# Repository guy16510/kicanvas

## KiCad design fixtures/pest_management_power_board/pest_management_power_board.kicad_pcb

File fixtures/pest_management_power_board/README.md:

# Pest Management Power Distribution Board

Rev B KiCad fixture for a low-voltage battery/control board that interfaces to a sealed commercial high-voltage DC/DC module used with a three-layer insect mesh.

## Rev B design goal

The battery source is treated as a protected 2S pack with **unknown cell current capability**. The PCB is therefore designed to minimize low-voltage losses and support short module-input transients, while a replaceable input fuse deliberately limits battery current.

This revision does **not** assume miscellaneous 18650 cells are safely capable of 5 A. Do not assemble unmatched loose cells into a 2S pack. Use a BMS/protected pack and begin with the conservative fuse value in the BOM.

## Electrical architecture

- Protected 2S Li-ion input, 7.4 V nominal / 8.4 V fully charged
- F1: 5x20 mm fast fuse, **start at 2 A** because cell capability is unknown
- SW1: panel-mounted momentary switch with an oversized low-resistance DC current path
- C1 + C2: two 2200 uF / 16 V low-ESR capacitors in parallel at the HV-module input
- C3: 1 uF / 25 V fast bypass capacitor across the switched module input
- Total bulk capacitance: nominal 4400 uF
- 3.0 mm low-voltage power traces to reduce distribution loss
- J2, 4-position isolated landing interface to a sealed commercial HV module
  - Pin 1: +7.4V_SW
  - Pin 2: GND
  - Pin 3: HV_POS
  - Pin 4: HV_NEG
- J3: HV_POS external mesh terminal
- J4: HV_NEG external mesh terminal

## What the larger capacitor bank does

The C1/C2 bank does not create additional sustained power. It stores a small amount of energy locally and can reduce battery-voltage sag during a short input-current transient from the commercial HV module. Sustained output power is still limited by the cells, BMS, fuse and module efficiency.

At 8.4 V, 4400 uF stores roughly 0.16 joule. At 7.4 V it stores roughly 0.12 joule. This is useful as a local transient reservoir, not as a substitute for a higher-power battery pack.

## PCB constraints

- `LV_Power`: battery, fuse, switch, capacitor bank, module input and return
- `HV_Grid`: commercial module HV output to J3/J4
- `HV_Grid` minimum clearance: 10.0 mm
- HV_POS and HV_NEG run in separate straight corridors
- A 2 mm-wide routed Edge.Cuts slot runs between the two HV corridors
- LV routing is kept left of the HV_POS corridor with >10 mm intended copper-edge spacing

## Power strategy with the same batteries

1. Reduce resistance in the low-voltage path using larger pads, 3 mm traces and an oversized switch contact path.
2. Put low-ESR bulk capacitance physically close to the module input.
3. Let the fuse control maximum battery current. Start at 2 A with unknown cells.
4. The sealed commercial HV module remains the component that determines sustained mesh voltage/current and recovery rate.

## Safety note

The board does not generate high voltage. It only distributes low-voltage battery power and interfaces to a sealed, commercially manufactured high-voltage module. Actual HV connector ratings, spacing, enclosure design, touch protection, discharge behavior and compliance must be validated against the selected module's maximum output voltage and applicable product-safety standards before fabrication or use.

The PCB being physically capable of carrying several amps does not mean unknown 18650 cells can safely supply that current.

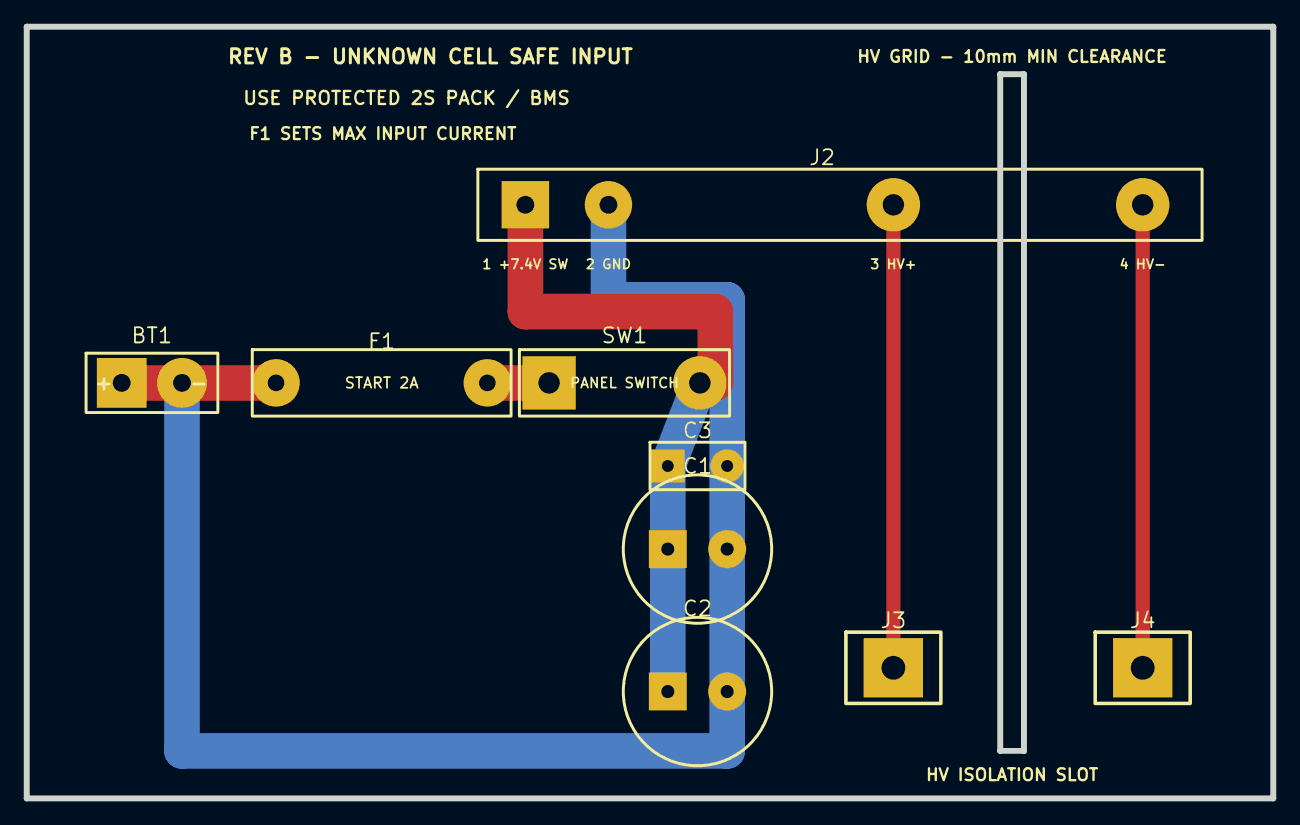
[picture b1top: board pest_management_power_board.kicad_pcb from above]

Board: 2 copper layers, 105.0 x 65.0 mm, 9 parts (0 on the bottom side), 6 nets.

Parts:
BT1: PROTECTED_2S_18650_7.4V; BATTERY_2S_INPUT_5P08
C1, C2: 2200uF_16V_LOW_ESR; CP_RADIAL_12P5MM_P5
C3: 1uF_25V_FILM; FILM_CAP_P5
F1: START_2A_FAST_MAX_AFTER_CELL_VALIDATION; FUSE_5X20_CLIP_17.8MM
J2: SEALED_COMMERCIAL_HV_MODULE_INTERFACE; HV_MODULE_4PIN_ISOLATED
J3: HV_POS_GRID; HV_GRID_SINGLE_SCREW_TERMINAL
J4: HV_NEG_GRID; HV_GRID_SINGLE_SCREW_TERMINAL
SW1: MOMENTARY_NO_10A_DC_PATH; PANEL_SWITCH_10A_LEADS

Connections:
+7V4_BAT: BT1.1, F1.1
+7V4_FUSED: F1.2, SW1.1
+7V4_SW: C1.1, C2.1, C3.1, J2.1, SW1.2
GND: BT1.2, C1.2, C2.2, C3.2, J2.2
HV_NEG: J2.4, J4.1
HV_POS: J2.3, J3.1

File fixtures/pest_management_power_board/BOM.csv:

Reference,Qty,Function,Specification,Recommended Part / Family,Notes
BT1,1,Battery input,2S Li-ion 7.4V nominal input; connector rated >=5A,"Phoenix Contact MKDS 1,5/2 family or equivalent 2-position 5.08mm terminal",Use protected 2S pack/BMS; connector and wiring must be rated for pack fault current
F1,1,Overcurrent fuse,5A fast-acting 5x20mm cartridge,"Littelfuse 217 Series, 5A fast-acting, e.g. 0217005.MXP",Confirm interrupt rating is appropriate for the selected battery pack
F1-HOLDER,1,Fuse holder,5x20mm PCB clip/holder rated >=5A,"Bel / Stewart FC-203-22 style 5x20mm holder or equivalent",PCB footprint uses 17.8mm lead spacing
SW1,1,Momentary pushbutton,Normally-open momentary; >=5A DC continuous at the actual battery voltage,"Panel-mount industrial momentary switch, 5A DC minimum",Board uses two heavy through-hole lead pads rather than a low-current tactile switch footprint; select final MPN by verified DC rating
C1,1,Bulk decoupling capacitor,470uF 25V radial electrolytic; 105C preferred,"Panasonic FR/FC series or Nichicon PW/HE equivalent, 470uF 25V",PCB footprint assumes approximately 10mm diameter and 5mm lead pitch; confirm dimensions before fabrication
J2,1,Commercial HV module interface,4 electrical positions: Pin1 +7.4V_SW; Pin2 GND; Pin3 HV_POS; Pin4 HV_NEG,"Custom isolated 4-position interface / flying-lead landing pads",HV pins are intentionally separated from LV pins and from one another; do not substitute a standard 5mm-pitch 4-position block
J3,1,HV positive grid output,Single heavy screw terminal; voltage rating >= selected module maximum output,"HV-rated single-position barrier/screw terminal",Final MPN cannot be selected safely until module maximum output voltage and required creepage category are known
J4,1,HV negative grid output,Single heavy screw terminal; voltage rating >= selected module maximum output,"HV-rated single-position barrier/screw terminal",Final MPN cannot be selected safely until module maximum output voltage and required creepage category are known
HV-MODULE,1,Isolated high-voltage source,Sealed pre-fabricated commercial DC/DC step-up module; 7.4V-compatible input,"User-selected commercial encapsulated module",Not designed or fabricated on this PCB; verify output voltage/current, insulation rating, discharge behavior, enclosure and connector requirements
PCB,1,Printed circuit board,2-layer FR4 1.6mm; routed isolation slot; 10mm HV clearance rule,"Custom PCB",Use routed mechanical slot exactly as Edge.Cuts; fabrication drawing should explicitly call out slot

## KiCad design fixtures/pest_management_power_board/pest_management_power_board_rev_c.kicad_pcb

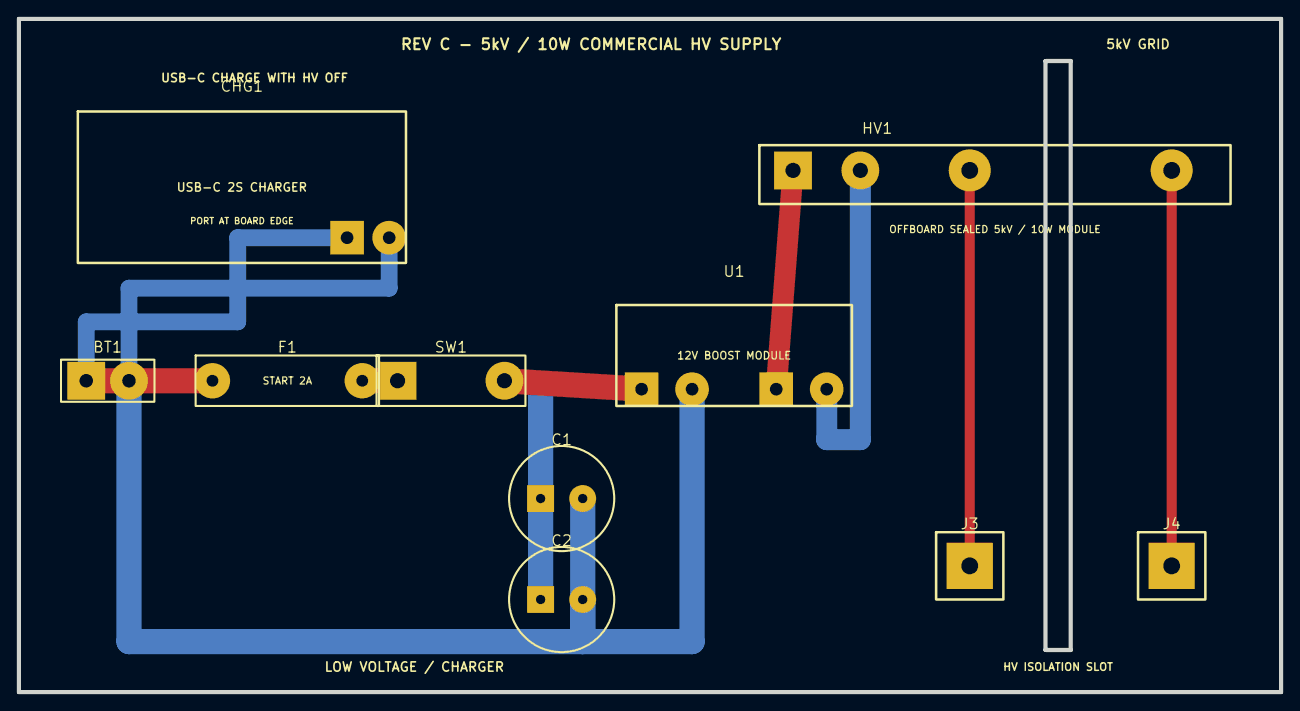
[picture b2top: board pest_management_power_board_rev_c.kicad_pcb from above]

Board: 2 copper layers, 150.0 x 80.0 mm, 10 parts (0 on the bottom side), 7 nets.

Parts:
BT1: PROTECTED_BALANCED_2S_PACK; PROTECTED_2S_PACK_INPUT
C1, C2: 2200uF_16V_LOW_ESR; CP_RADIAL_12P5_P5
CHG1: USB-C_5V_TO_2S_8V4_1A; USB_C_2S_CHARGER_DAUGHTERBOARD_39X18
F1: 2A_FAST_START; FUSE_5X20_CLIP_17P8
HV1: ANALOG_TECH_AHV12V5KV2MAW_OFFBOARD; AHV12V5KV2MAW_INTERFACE
J3: HV_POS_GRID; HV_GRID_SINGLE_TERMINAL
J4: HV_NEG_GRID; HV_GRID_SINGLE_TERMINAL
SW1: HV_ENABLE_MOMENTARY; PANEL_SWITCH_HEAVY
U1: POLOLU_U3V70F12_12V_BOOST; POLULU_U3V70F12_INTERFACE

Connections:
+12V_HV: HV1.1, U1.3
BAT_FUSED: F1.2, SW1.1
BAT_P: BT1.1, CHG1.1, F1.1
BAT_SW: C1.1, C2.1, SW1.2, U1.1
GND: BT1.2, C1.2, C2.2, CHG1.2, HV1.2, U1.2, U1.4
HV_NEG: HV1.4, J4.1
HV_POS: HV1.3, J3.1

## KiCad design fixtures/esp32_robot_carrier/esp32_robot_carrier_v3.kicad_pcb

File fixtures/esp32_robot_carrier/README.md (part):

# ESP32 robot carrier: 36–42 V input, 5 V/24 V power, and battery sensing

The generated v3 carrier accepts a 36–42 V battery, protects the input with the
LTC4367 stage, and feeds two isolated through-hole DC-DC modules: a regulated
5.10 V nominal rail for the Raspberry Pi, ESP32 peripherals, sensors, and RGB pixels, plus
a separately fused 24 V / 2.5 A rail for a servo. The protected battery voltage
is exposed to the ESP32 on GPIO34. A dual rail-to-rail amplifier lets the two
ESP32 DACs cover the exact WinXu controllers' approximately 1.1–4.2 V throttle
range. Four PhotoMOS relays provide floating
two-wire brake and reverse contacts for the two motor controllers. The older v2
fixture remains a 5 V-only board and must never be connected directly to the
36–42 V battery.

The front silkscreen identifies the product as **Trashbot v1** and the maker as
**Burns Industries**, while retaining `CARRIER rev3` as the PCB revision.
Use [`WIRING_HARNESS.md`](WIRING_HARNESS.md) as the single assembly map for
power, both WinXu controllers, Hall taps, ultrasonic modules, RGB, servo, Pi
USB, and every exposed ESP32 socket pin.

## Safety

36–42 V battery packs can supply destructive fault current. Fit the specified
fuse, verify polarity before connecting the pack, and test a first assembly from
a current-limited bench supply. Do not bypass the protection FETs or replace the
series ADC resistors with jumpers. Confirm the selected 0805 resistors have a
working-voltage rating of at least 50 V; the two top resistors split the possible
surge voltage.

This circuit estimates remaining usable energy from terminal voltage. It is not
a cell-level battery-management system and cannot replace the pack BMS.

## Replaceable fuse holders

The v3 board has three replaceable 5×20 mm through-hole fuse positions. All use
the 22 mm lead-pitch footprint for Littelfuse `0PTF0015P`, a 250 V, 6.3 A-rated
PCB holder. See the
[manufacturer data sheet](https://www.littelfuse.com/assetdocs/littelfuse_fuse_block_ptf015_datasheet.pdf?assetguid=4413c71d-437b-411b-9c0c-09971540e8fc).

| Reference | Protected circuit | Fuse requirement |
| --- | --- | --- |
| F1 | `J_BAT` positive input, before the TVS, LTC4367, MOSFETs, and both converters | Eaton Bussmann `S505H-5-R`: 5 A time-delay ceramic, 5×20 mm, 400 VDC |
| F2 | Both positive pins of `J_PI_PWR` only | Eaton Bussmann `S505H-5-R`: 5 A time-delay ceramic, 5×20 mm, 400 VDC; use wiring rated for at least 5 A |
| F3 | 24 V servo output before the ferrite, `J_SERVO`, and `J_24V_AUX` | Eaton Bussmann `S505H-3.15-R`: 3.15 A time-delay ceramic, 5×20 mm, 400 VDC |

Do not install a common 32 V automotive blade fuse at F1: a 42 V pack exceeds
that voltage rating. The fuse link—not only the holder—must have a suitable DC
voltage rating and DC breaking capacity for the pack's available fault current.
The selected S505H links have a 1500 A interrupt rating at 400 VDC; see the
[Eaton S505H data sheet](https://www.eaton.com/content/dam/eaton/products/electronic-components/resources/data-sheet/eaton-s505h-vac-time-delay-fuses-data-sheet.pdf).
F2 and F3 do not increase converter capacity. The 5 V consumers must fit within
the Murata module's 8 A low-line rating at the bottom of the pack. At higher
input voltage, the 5.10 V trim makes the data sheet's 50 W output-power limit
9.80 A rather than 10 A; the
servo and auxiliary 24 V load share the Traco module's 2.5 A maximum. The F3
link is intentionally rated above the converter's normal full-load current to
avoid nuisance opening; it does not authorize a 3.15 A continuous load.

F1 protects the carrier after the battery connector. It cannot protect the
battery cable before `J_BAT`, so install an additional appropriately rated
pack-side fuse as close to battery positive as practical. Never bypass any
holder with wire or solder. The two 350 W / 18 A motor controllers remain
outside this carrier and each needs its own pack-side branch fuse and wiring.

## Battery-sense circuit

| Reference | Value | Connection | Purpose |
| --- | --- | --- | --- |
| R40 | 240 kΩ, 1%, 0805 | `VIN_PROTECTED` to `BATTERY_DIVIDER_MID` | First high-side resistor |
| R41 | 240 kΩ, 1%, 0805 | `BATTERY_DIVIDER_MID` to `BATTERY_ADC_GPIO34` | Second high-side resistor |
| R42 | 20 kΩ, 1%, 0805 | `BATTERY_ADC_GPIO34` to GND | Divider bottom |
| C20 | 100 nF | `BATTERY_ADC_GPIO34` to GND | ADC reservoir/noise filter |

The divider is connected after the LTC4367 protection FETs. If input protection
disconnects the pack, the divider cannot back-power an otherwise unpowered ESP32
through GPIO34.

The scale factor is exactly 25 with nominal values:

```text
Vbattery = Vgpio34 × (240k + 240k + 20k) / 20k
         = Vgpio34 × 25
```

| Protected battery | GPIO34 nominal |
| ---: | ---: |
| 36.0 V | 1.44 V |
| 39.0 V | 1.56 V |
| 42.0 V | 1.68 V |

The divider draws 84 µA at 42 V. Its Thevenin resistance is 19.2 kΩ, and C20
gives a nominal 1.92 ms time constant. Average multiple readings and allow at
least 10 ms after power-up or a major load transition before treating a sample as
settled.

The v3 input uses an SMCJ48A TVS. Littelfuse specifies a 77.4 V maximum clamp at
the rated peak pulse current. The nominal divider output at that clamp is 3.096 V;
with 1% worst-case resistor tolerance it remains about 3.16 V. See the
[Littelfuse SMCJ data sheet](https://m.littelfuse.com/~/media/electronics/datasheets/tvs_diodes/littelfuse_tvs_diode_smcj_datasheet.pdf.pdf).
This is transient headroom, not permission to apply more than the carrier's
specified 42 V maximum continuously.

## Pin assignment change

GPIO34 is `ADC1_CH6`, input-only, and is not a boot strap. ADC1 was selected so
the measurement remains available when Wi-Fi is running; Espressif documents
that ADC2 pins cannot be used with Wi-Fi. See the
[ESP32 GPIO table](https://docs.espressif.com/projects/esp-idf/en/v4.4.1/esp32/api-reference/peripherals/gpio.html).

| Function | v2 | v3 with battery sensing |
| --- | --- | --- |
| Battery voltage | Not available | GPIO34 / ADC1_CH6 |
| Front ultrasonic echo | GPIO34 | GPIO33 |
| Left brake | GPIO33 | GPIO12 / pulled-down boot strap |
| UART0 transmit/logging | GPIO1 | GPIO1, unchanged |
| UART0 receive / Pi commands | GPIO3 | GPIO3, preserved |

All three echoes pass through the linked project's 10 kΩ/15 kΩ 5 V-to-3.3 V
divider. The externally driven front echo is on non-strapping GPIO33. GPIO12 is
instead the left-brake output: it sees only the local 330 Ω PhotoMOS LED path
and a 100 kΩ pull-down, which keeps the flash-voltage strap low during reset.
The motor-controller contact remains electrically floating. UART0 remains
dedicated to GPIO1/GPIO3 for the linked firmware's
bidirectional Raspberry Pi command protocol, ROM logs, flashing, and USB serial
diagnostics.

### JSN-SR04T / AJ-SR04M ultrasonic contract

JSN-SR04T and AJ-SR04M are ultrasonic distance sensors; they are separate from
the three Hall-position signals inside each hoverboard motor. The carrier powers
each ultrasonic module from 5 V and provides this four-wire interface:

| Sensor pin | Carrier connection |
| --- | --- |
| VCC | `+5V` |
| GND | GND |
| TRIG/RX | 5 V output from a dedicated 74AHCT1G125 buffer |
| ECHO/TX | 10 kΩ/15 kΩ divider to the assigned ESP32 echo GPIO |

The three trigger buffers are `U_TRIG_L`, `U_TRIG_F`, and `U_TRIG_R`, each with
its own 100 nF bypass capacitor. Their AHCT inputs recognize the ESP32's 3.3 V
logic, while their outputs provide an unambiguous 5 V-class trigger. At the
5.10 V nominal carrier rail, the nominal echo voltage after the divider is
3.06 V; at the sensor's 5.5 V maximum supply it is 3.30 V nominal. Do not power
one of these modules from 3.3 V while leaving the divider installed: the divided
echo may then be too low for a guaranteed ESP32 logic high.

Configure each module for ordinary trigger/echo pulse-width mode, not UART,
automatic-output, switch, or low-power serial mode. On AJ-SR04M V2.0 this means
R19 is open/NC. JSN-SR04T mode selection varies by board revision, so confirm
that the installed revision is in its HC-SR04-compatible trigger/echo mode. The
[AJ-SR04M V2.0 specification](https://offer-product.oss-cn-beijing.aliyuncs.com/product/offer/attachment/2211620956069/file/subPdf_485493_241735_20230310-173148512.pdf)
lists 3–5.5 V operation, a trigger-high requirement up to 0.7×VCC, a 20 cm blind
zone, and a 50 ms measurement cycle. The
[JSN-SR04T specification](https://img.ozdisan.com/ETicaret_Dosya/951866_220247.pdf)
specifies 5 V operation, approximately 30 mA working current, and a roughly
25 cm blind zone.

Firmware should hold every trigger LOW at startup, generate a conservative
20 µs HIGH pulse, fire only one ultrasonic sensor at a time, and leave at least
60 ms between transmitted pings. Use an echo timeout appropriate to the maximum
distance you actually need; a 6 m round-trip pulse can last about 35 ms. The
20–25 cm blind zone means these modules cannot be the robot's only last-resort
collision detector—retain a physical bumper or a separate short-range sensor.
Only the probe/cable is intended for exposed wet locations; enclose the sensor
PCB and connector against water and conductive debris.

GPIO5 and GPIO15 have internal boot-time pulls, and the AHCT inputs are
deliberately high impedance so they do not alter ESP32 strap levels. This means
one or more buffered TRIG outputs can be HIGH briefly before firmware configures
the GPIOs. Treat all startup echoes as invalid, initialize all three triggers
LOW before enabling the ranging scheduler, wait at least 60 ms, and then begin
one-at-a-time pings. Do not add external strap pull resistors to these pins.

The linked [hoverboard-robot firmware](https://github.com/guy16510/hoverboard-robot),
reviewed at `board_config.h` commit `94c58a4` on 2026-08-10, still defines
`kFrontEchoPin = 34` and `kLeftBrakePin = 33`. They must be changed
to GPIO33 and GPIO12 respectively before this board and that firmware are used
together. Add GPIO34 as the battery ADC pin to the firmware's uniqueness list at
the same time. Without that migration, the firmware will interpret battery
voltage as an ultrasonic echo, will not read the actual front sensor, and will
drive the wrong left-brake pin.

In `firmware/esp32/board_config.h`, the migration must also update the comment
and the existing `static_assert` that currently requires all three echo pins to
be 34 or higher. A safe firmware contract should explicitly assert that
left/right echoes remain on GPIO35/GPIO39, front echo is GPIO33, left brake is
GPIO12, battery ADC is GPIO34, and every assigned pin remains unique. It should
also reject GPIO1/GPIO3 for every sensor or actuator because UART0 owns them.
Keep every ultrasonic trigger LOW through initialization; the current
`UltrasonicArray::begin()` already does this.

The repository's current `board_config.h` already uses GPIO5/GPIO15/GPIO18 for
front/left/right trigger and GPIO16/GPIO17 for left Hall A/B, which matches this
carrier. Its top-level README and `docs/WIRING.md` still show the older trigger
assignment on GPIO16/GPIO17, so code constants—not those stale diagrams—are the
firmware source of truth. Increase `kUltrasonicPingSpacingMs` from 40 ms to at
least 60 ms for the installed waterproof modules, and enable
`kLeftHallEnabled` only after all three left Hall taps are physically verified.

## ESP32 socket and firmware contract

The carrier accepts the common **30-pin ESP32 DevKit V1 / `esp32dev`** layout
using an ESP32-WROOM-32-class module,
with 15 pins per side on 2.54 mm pitch and 25.4 mm between header centerlines.
It is not the 38-pin Espressif DevKitC V4 footprint. The antenna is at the pad-1
end of the two sockets and the USB connector is at the pad-15 end. Compare the
labels on the actual ESP32 board before inserting it; installing a different
variant or rotating the module can put 5 V on an I/O pin.
Do not substitute an ESP32-WROVER/PSRAM module: those variants can reserve
GPIO16/GPIO17 internally, while this carrier uses both pins for left motor Hall
signals. Before assembly, place the unpowered DevKit over a 1:1 print or the
bare sockets and verify all 30 labels, 2.54 mm pitch, 25.4 mm row spacing,
antenna end, and USB end without soldering it in place.

The carrier reserves a 29.4 × 11 mm copper/track/via keepout on both layers
from x=48–77.4 mm and y=13–24 mm beneath the DevKit antenna end. Do not place a
metal standoff, cable shield, battery, controller case, or conductive chassis
directly over that antenna region. The keepout preserves RF clearance on the
carrier; the final enclosure still needs a Wi-Fi/Bluetooth range test.

The executable system validator enforces this exact physical mapping. `EN` is
intentionally unconnected, and ESP32 VIN is isolated from carrier 5 V by
`JP_ESP_PWR`:

| Pad | `J_ESP_L` DevKit pin → carrier net | Pad | `J_ESP_R` DevKit pin → carrier net |
| ---: | --- | ---: | --- |
| 1 | EN → unconnected | 1 | 3V3 → `+3V3` |
| 2 | GPIO36 → left Hall C | 2 | GND → GND |
| 3 | GPIO39 → right echo | 3 | GPIO15 → buffered left trigger |
| 4 | GPIO34 → battery ADC | 4 | GPIO2 → RGB buffer only |
| 5 | GPIO35 → left echo | 5 | GPIO4 → MPU SDA reserve |
| 6 | GPIO32 → right brake | 6 | GPIO16 → left Hall A |
| 7 | GPIO33 → front echo | 7 | GPIO17 → left Hall B |
| 8 | GPIO25 → left throttle DAC | 8 | GPIO5 → buffered front trigger |
| 9 | GPIO26 → right throttle DAC | 9 | GPIO18 → buffered right trigger |
| 10 | GPIO27 → left reverse | 10 | GPIO19 → right Hall A |
| 11 | GPIO14 → right reverse | 11 | GPIO21 → right Hall B |
| 12 | GPIO12 → left brake | 12 | GPIO3/RX0 → Pi/USB serial RX |
| 13 | GPIO13 → servo | 13 | GPIO1/TX0 → Pi/USB serial TX |
| 14 | GND → GND | 14 | GPIO22 → right Hall C |
| 15 | VIN → `ESP32_VIN_USB_ISOLATED` | 15 | GPIO23 → MPU SCL reserve |

| Function | GPIO | Carrier interface | hoverboard-robot status |
| --- | ---: | --- | --- |
| Left throttle DAC | 25 | 1 kΩ/1 µF filter, TLV9002 ×1.2745, 330 Ω output, dual fail-safe pull-downs | Firmware constants must account for gain |
| Right throttle DAC | 26 | 1 kΩ/1 µF filter, TLV9002 ×1.2745, 330 Ω output, dual fail-safe pull-downs | Firmware constants must account for gain |
| Left reverse | 27 | 330 Ω LED drive, 100 kΩ pull-down, AQY212SX floating two-wire contact | Active; use only the labelled reverse pair |
| Right reverse | 14 | 330 Ω LED drive, 100 kΩ pull-down, AQY212SX floating two-wire contact | Active; use only the labelled reverse pair |
| Left brake | 12 | 330 Ω LED drive, 100 kΩ pull-down, AQY212SX floating two-wire contact | Firmware migration required |
| Right brake | 32 | 330 Ω LED drive, 100 kΩ pull-down, AQY212SX floating two-wire contact | Active |
| Left Hall A/B/C | 16 / 17 / 36 | Three 10 kΩ/12 kΩ dividers and individual 10 nF filters | Disabled until `kLeftHallEnabled = true` |
| Front ultrasonic | TRIG 5 / ECHO 33 | 74AHCT 5 V trigger; 10 kΩ/15 kΩ echo divider | Firmware migration required |
| Left ultrasonic | TRIG 15 / ECHO 35 | 74AHCT 5 V trigger; 10 kΩ/15 kΩ echo divider | Active |
| Right ultrasonic | TRIG 18 / ECHO 39 | 74AHCT 5 V trigger; 10 kΩ/15 kΩ echo divider | Active |
| MPU6050 | SDA 4 / SCL 23 | Breakout pads | Reserved, not implemented |
| Servo | 13 | 3.3 V signal with 100 kΩ reset pull-down, separately fused/filtered 24 V, ground | One direct channel; firmware addition required |
| RGB data | 2 | 74AHCT1G125 high-impedance input, 330 Ω cable resistor; no auxiliary pad | Carrier hardware only |
| Battery voltage | 34 / ADC1_CH6 | 25:1 divider and 100 nF | Firmware addition required |
| UART0 receive / Pi commands | 3 | Passive breakout only | Reserved for DevKit USB-to-UART |
| UART0 transmit / logs | 1 | Passive breakout only | Reserved for DevKit USB-to-UART |

RGB uses exactly one data line: GPIO2 feeds the 74AHCT1G125, then a 330 Ω
connector-side resistor feeds `RGB_DATA_OUT`. The connector also has 5 V,
ground, and a local 1000 µF / 10 V through-hole bulk capacitor with a marked
positive pad. Addressable pixels must be daisy-chained; the three connector
pads are power, one data signal, and ground—not separate red/green/blue PWM
channels.

Each Hall channel has its own small 10 nF capacitor from the divided GPIO node
to ground, placed beside the lower divider resistor. With 10 kΩ/12 kΩ the
nominal Hall high is 2.73 V at a 5.0 V source; even a 5.5 V source and opposing
1% resistor tolerances remain about 3.05 V. The divider's nominal Thevenin
resistance is 5.45 kΩ, so the 10 nF filter pole is about 2.9 kHz—well above the
roughly 240 Hall transitions/s observed in the linked project while providing
useful suppression of motor-edge noise.

GPIO5 and GPIO15 are boot-strapping pins but only drive high-impedance
ultrasonic TRIG inputs. GPIO2 and GPIO12 are also strapping pins. GPIO2 now has
no external auxiliary pad and drives only the high-impedance RGB buffer input.
GPIO12 drives only the left-brake PhotoMOS LED through 330 Ω; its input node has
a 100 kΩ pull-down and the output contact is isolated. Do not attach other
circuits that force any strap pin during reset. GPIO34, GPIO35, GPIO36, and
GPIO39 are input-only; the carrier uses them only as inputs. GPIO6–GPIO11, which
the ESP32 module uses for flash, are not present in the carrier pin contract.

Classic ESP32 silicon has a documented erratum in which powering SAR ADC1 or
ADC2 can pull GPIO36 and GPIO39 low for about 80 ns. This matters because the
board reads battery voltage with ADC1 while GPIO36 is a Hall interrupt input and
GPIO39 is the right ultrasonic echo. The Hall RC helps reject short external
noise, but firmware must still follow Espressif's workaround: keep ADC power
acquired while Hall interrupts are active (or ignore GPIO36/GPIO39 events around
ADC power transitions) and reject impossible Hall states/skips. Verify this on
the exact DevKit revision before enabling the left Hall channel.

### USB serial, JTAG, and ESP32 power selection

The Raspberry Pi's USB connection uses the DevKit's USB-to-UART bridge and
therefore GPIO1 (`TX0`) and GPIO3 (`RX0`). The carrier connects those nets only
to passive breakout pads—no sensor, motor control, LED, servo, or battery circuit
loads them. This preserves boot logging, flashing, diagnostics, Pi commands, and
telemetry over the same USB serial port.

USB serial is not the same as external JTAG. The classic ESP32's default JTAG
pins are GPIO12–GPIO15; this design uses them for left brake, servo, right
reverse, and left ultrasonic trigger. USB serial debugging remains fully
available, but four-wire JTAG is **not available** with the present feature set.
Preserving JTAG would require a larger redesign, such as moving several
low-speed outputs to an I/O/PWM expander.

`JP_ESP_PWR` prevents the Pi's USB 5 V and the carrier's 5 V rail from being
hard-wired together. It is a normally-open solder jumper and its safe modes are:

| Pi/USB state | `JP_ESP_PWR` | ESP32 power source |
| --- | --- | --- |
| Normal Pi USB cable connected | **Open** | USB VBUS from the Pi |
| No USB cable connected | Closed | Carrier 5 V through the DevKit VIN pin |
| Verified data-only USB cable with VBUS physically absent | Closed | Carrier 5 V through VIN |

Never close `JP_ESP_PWR` while a normal powered USB cable is connected. Never
apply a separate supply to the ESP32's 3.3 V header. Espressif explicitly lists
USB, 5 V-header, and 3.3 V-header power as mutually exclusive because combining
them can damage the board or a source. The carrier socket targets a common
third-party 30-pin `esp32dev`, whose exact USB power circuit can vary, so the
jumper is required instead of assuming that a particular clone contains a safe
isolation diode. See Espressif's
[DevKit power warning](https://docs.espressif.com/projects/esp-idf/en/v5.1.2/esp32/hw-reference/esp32/get-started-devkitc.html)
and [GPIO restriction table](https://docs.espressif.com/projects/esp-idf/en/latest/esp32/api-reference/peripherals/gpio.html).

## 36–42 V to 5 V and 24 V power budget

The final power paths are:

```text
J_BAT -> F1 S505H 5 A / 400 VDC -> SMCJ48A -> LTC4367
      -> back-to-back 100 V MOSFETs -> VIN_PROTECTED

VIN_PROTECTED -> PS1 Murata UWS-5/10-Q48N-C + R44 trim -> 5.10 V nominal
              -> F2 5 A -> J_PI_PWR
              -> sensors, ESP32-side logic, and RGB output

VIN_PROTECTED -> PS2 Traco TEN 60-4815WIN -> 24 V
              -> F3 3.15 A -> FB2 -> J_SERVO + J_24V_AUX
```

The LTC4367 window is approximately 30 V undervoltage rising and 50 V
overvoltage. PS1 accepts 18–75 V and is trimmed to about 5.10 V. Use its 8 A
low-line current ceiling at the bottom of the pack. Above 36 V, the nominal
10 A current rating is reduced to 9.80 A by the data sheet's 50 W maximum-output-
power rule (`50 W / 5.099 V`). Pin 2 is tied to `-VIN` to turn its negative-logic remote input
on, sense pins are tied locally to their respective outputs, and R44 = 806 kΩ
connects Trim to ground/`-Sense`. Murata's trim-up equation gives approximately
5.099 V nominal, providing Raspberry Pi cable-drop margin while remaining below
the Pi's 5.25 V maximum. Measure the assembled rail under no-load and 5 A load;
do not populate a lower trim resistance without recalculating worst-case module
and resistor tolerance. PS2 also accepts 18–75 V and supplies 24 V at 2.5 A.
Its positive-logic Remote pin is left open for on and Trim is left open for
nominal 24 V. Both modules are isolated parts, but their input and output
negative pins are intentionally joined to carrier ground; the completed carrier
is therefore not a galvanically isolated system. The implemented pin contracts
come from the official
[Murata UWS data sheet](https://pim.murata.com/asset/pim4/isolatedDCDCconverter/UWS_PDF_ISOLATEDDCDCCONVERTER?lastModifiedDatetime=20250707193640)
and [Traco TEN 60WIN data sheet](https://www.tracopower.com/products/ten60win.pdf).

PS1 has C10 (22 µF / 100 V) and C11 (4.7 µF / 100 V) on its input, plus C18
(1 µF / 50 V ceramic) and C16 (470 µF / 10 V) on its output. PS2 has C26
(22 µF / 100 V) on its input, C25 (1 µF / 50 V) directly on its output, and C19
(470 µF / 50 V) after F3 and FB2 at the servo connector. D2 is an SMBJ26A
unidirectional TVS on that fused rail (cathode to +24 V) to absorb short servo
regeneration spikes; it is not a continuous braking dump load. Module pin spacing,
drill diameters, body outlines, and courtyards match the manufacturers' THT
drawings. Do not place hardware, wires, or conductive chassis parts in either
module courtyard or underneath the modules.

At simultaneous nominal full load the modules deliver 50 W + 60 W. Allowing for
conversion loss, the carrier can draw roughly 3.4 A from a 36 V pack; transient
and startup current can be higher. The shared 5 A time-delay F1 provides useful
margin while remaining below the 6.3 A holder rating, but the exact fuse choice
must still be proven against startup, worst-case temperature, and the actual
pack's available fault current. Murata's application guidance calls for an
external input fuse and may show a fast-blow fuse; this board intentionally uses
the high-DC-interrupt S505H time-delay family to tolerate two-module startup.
Treat that as a first-article validation item, not as a paper-only conclusion.

The 5 V load budget is independent of the servo rail:

```text
I5V = Ipi,max + Iesp32/accessory + Isensors + (0.060 A × RGB pixels)
I5V <= 8.0 A at the bottom of the pack
I5V <= 9.80 A only above 36 V and after thermal qualification
```

The 60 mA-per-pixel RGB term is a conservative full-white estimate; use the
actual LED data sheet and a firmware brightness cap. If the Pi branch uses its
full 5 A allowance at the bottom of the pack, only 3 A of the guaranteed 5 V
capacity remains for every other 5 V load. F2 protects only the Pi connector;
it does not reserve 5 A or increase converter capacity.

The 24 V rail has a separate limit:

```text
Iservo,stall + I24V_aux <= 2.5 A, with thermal derating as required
```

`J_SERVO` is pad 1 signal/GPIO13, pad 2 fused 24 V, and pad 3 ground. R53 is a
100 kΩ pull-down that keeps the signal inactive while the ESP32 is unpowered or
in reset; firmware must still command a known-safe pulse before the servo rail
is enabled.
`J_24V_AUX` pad 1 is the same fused 24 V rail and pad 2 is ground. Confirm the
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
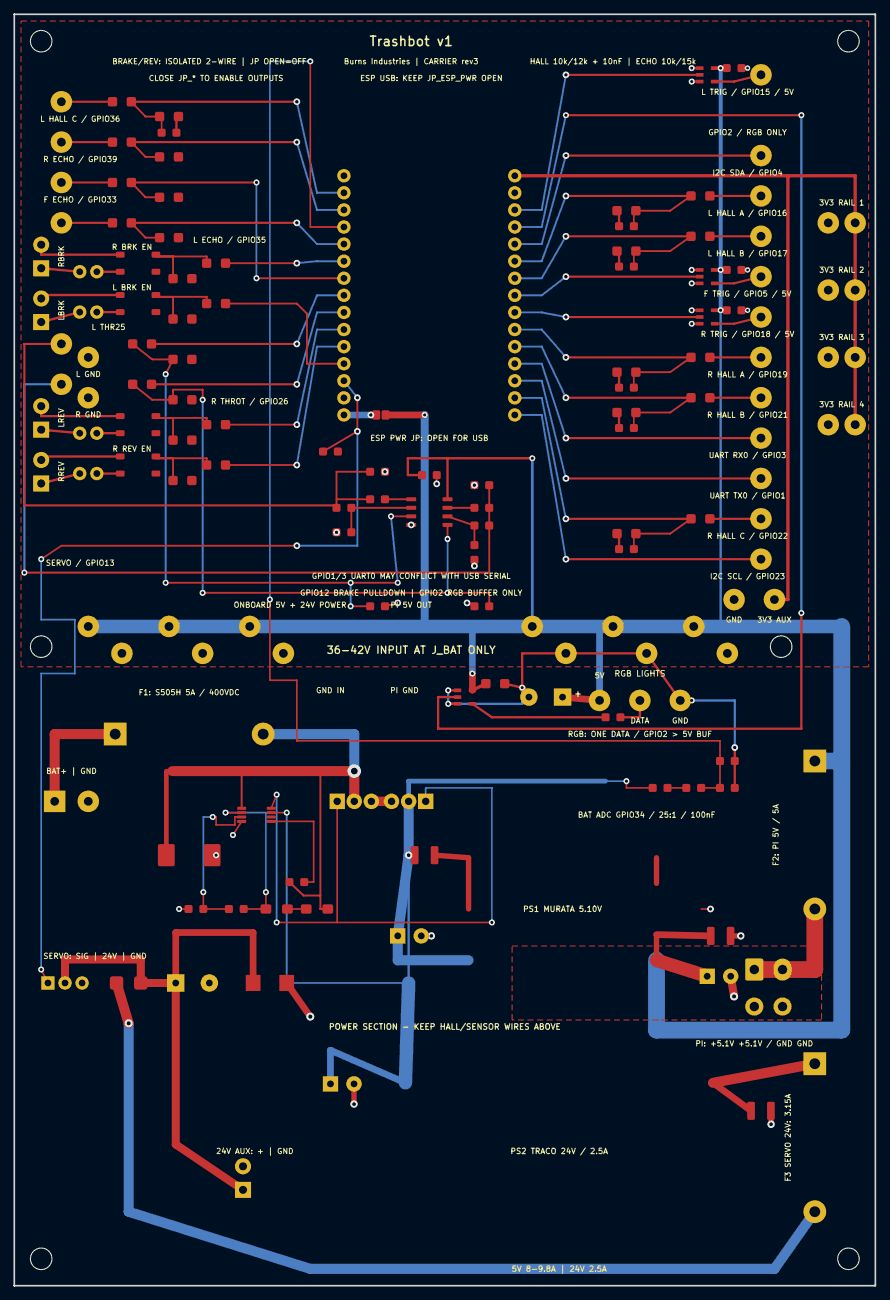
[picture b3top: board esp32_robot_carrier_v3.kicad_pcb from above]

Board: 2 copper layers, 128.0 x 189.0 mm, 154 parts (0 on the bottom side), 81 nets.

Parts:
C1, C2: 1uF; C_0805_2012Metric
C3: 100nF; C_0805_2012Metric
C4, C5, C6, C7, C8, C9: 10nF_HALL_RC; SMD2_1.2x1.2
C10: 22uF_100V_INPUT_BULK; CP_Radial_D8_P3.5
C11: 4.7uF_100V_X7R; SMD2_1.15x2.7
C16: 470uF_10V_OUTPUT; CP_Radial_D8_P3.5
C18: 1uF_50V_X7R_MODULE_OUTPUT; SMD2_1.15x2.7
C19: 470uF_50V_SERVO_BULK; CP_Radial_D12.5_P5
C20: 100nF_BAT_ADC_FILTER; C_0805_2012Metric
C21, C22, C23: 100nF_TRIGGER_BYPASS; R_0805_2012Metric
C24: 1000uF_10V_RGB_BULK; CP_Radial_D10_P5_RGB
C25: 1uF_50V_X7R_24V_MODULE_OUTPUT; C_1210_3225Metric
C26: 22uF_100V_24V_MODULE_INPUT; CP_Radial_D8_P3.5
C27: 100nF_THROTTLE_BYPASS; C_0805_2012Metric
D1: SMCJ48A_TVS; D_SMC_DO-214AB
D2: SMBJ26A_26V_SERVO_TVS; D_SMB_CUSTOM
F1: 0PTF0015P_5x20_INPUT_5A; Littelfuse_0PTF0015P_5x20
F2: 0PTF0015P_5x20_PI_5A; Littelfuse_0PTF0015P_5x20
F3: 0PTF0015P_5x20_SERVO_3.15A; Littelfuse_0PTF0015P_5x20
FB2: 6A_120R_FERRITE_SERVO; SMD2_2x2
H1, H2, H3, H4: M3; MountingHole_3.2mm
H5, H6: M3; MountingHole_3.2mm_M3
J3V3: 3V3_AUX; WirePad
J3V3_1: 3V3_RAIL_1; WirePad
J3V3_2: 3V3_RAIL_2; WirePad
J3V3_3: 3V3_RAIL_3; WirePad
J3V3_4: 3V3_RAIL_4; WirePad
JGND3: GND_AUX; WirePad
JGND3_1: GND_RAIL_1; WirePad
JGND3_2: GND_RAIL_2; WirePad
JGND3_3: GND_RAIL_3; WirePad
JGND3_4: GND_RAIL_4; WirePad
JP1G: GND_AUX_1; WirePad
JP1V: 5V_AUX_1; WirePad
JP2G: GND_AUX_2; WirePad
JP2V: 5V_AUX_2; WirePad
JP3G: GND_AUX_3; WirePad
JP3V: 5V_AUX_3; WirePad
JP4G: GND_AUX_4; WirePad
JP4V: 5V_AUX_4; WirePad
JP5G: GND_AUX_5; WirePad
JP5V: 5V_AUX_5; WirePad
JP6G: GND_AUX_6; WirePad
JP6V: 5V_AUX_6; WirePad
JP_ESP_PWR: OPEN_WHEN_USB_CONNECTED; SOLDER_JUMPER_OPEN
JP_LBRK: U7_OUTPUT_ENABLE; ENABLE_JUMPER_1x02
JP_LREV: U8_OUTPUT_ENABLE; ENABLE_JUMPER_1x02
JP_RBRK: U6_OUTPUT_ENABLE; ENABLE_JUMPER_1x02
JP_RREV: U9_OUTPUT_ENABLE; ENABLE_JUMPER_1x02
J_24V_AUX: 24V_SERVO_AUX_2.5A_SHARED; TerminalBlock_1x02_P3.50
J_BAT: 36-42V_BATTERY; PTH2_5
J_ESP_L: ESP32_DEVKIT_30PIN_SOCKET; ESP32_HEADER_1x15
J_ESP_R: ESP32_DEVKIT_30PIN_SOCKET; ESP32_HEADER_1x15
J_FECHO: FECHO_RAW; WirePad
J_FTRIG: FTRIG; WirePad
J_LBRK: L_BRAKE_FLOATING_CONTACT; TerminalBlock_1x02_P3.50
J_LCTRL_GND: CONTROLLER_SIGNAL_GND; WirePad
J_LECHO: LECHO_RAW; WirePad
J_LHALLA: LHALLA_RAW; WirePad
J_LHALLB: LHALLB_RAW; WirePad
J_LHALLC: LHALLC_RAW; WirePad
J_LREV: L_REVERSE_FLOATING_CONTACT; TerminalBlock_1x02_P3.50
J_LTHR: LTHR; WirePad
J_LTRIG: LTRIG; WirePad
J_PI_PWR: 5V_5A_FUSED_TO_PI; MiniFitJr_2x2
J_RBRK: R_BRAKE_FLOATING_CONTACT; TerminalBlock_1x02_P3.50
J_RCTRL_GND: CONTROLLER_SIGNAL_GND; WirePad
J_RECHO: RECHO_RAW; WirePad
J_RGB_5V: RGB_5V; WirePad
J_RGB_DATA: RGB_DATA_5V; WirePad
J_RGB_GND: RGB_GND; WirePad
J_RHALLA: RHALLA_RAW; WirePad
J_RHALLB: RHALLB_RAW; WirePad
J_RHALLC: RHALLC_RAW; WirePad
J_RREV: R_REVERSE_FLOATING_CONTACT; TerminalBlock_1x02_P3.50
J_RTHR: RTHR; WirePad
J_RTRIG: RTRIG; WirePad
J_RX0: RX0; WirePad
J_SCL: SCL; WirePad
J_SDA: SDA; WirePad
J_SERVO: SIG_24V_GND; Servo_1x03
J_TX0: TX0; WirePad
Q5, Q6: STP100N10F7_100V; TO-220-3
R1, R3, R5, R7, R19, R21, R23, R25, R27: 10k; R_0805_2012Metric
R2, R20, R22, R24, R26, R28: 12k_1pct_HALL; R_0805_2012Metric
R4, R6, R8: 15k_1pct_ULTRASONIC; R_0805_2012Metric
R9, R11, R15, R17: 100k; R_0805_2012Metric
R10, R12, R16, R18: 330R_PHOTOMOS_LED; R_0805_2012Metric
R13, R14: 1k; R_0805_2012Metric
R29, R30: 100k_THROTTLE_INPUT_FAILSAFE; R_0805_2012Metric
R35: 49.9k_1pct_OV_BOTTOM; SMD2_1.2x1.2
R36: 37.4k_1pct_UV_OV; SMD2_1.2x1.2
R37: 2.45M_1pct_UV_TOP_B; SMD2_1.6x1.4
R38: 2.45M_1pct_UV_TOP_A; SMD2_1.6x1.4
R39: 470k_SHDN_PULLUP; SMD2_1.2x1.2
R40: 240k_1pct_BAT_ADC_TOP_A; R_0805_2012Metric
R41: 240k_1pct_BAT_ADC_TOP_B; R_0805_2012Metric
R42: 20k_1pct_BAT_ADC_BOTTOM; R_0805_2012Metric
R43: 330R_RGB_DATA; R_0805_2012Metric
R45: 330R_L_THROTTLE_OUTPUT; R_0805_2012Metric
R46: 6.04k_1pct_L_THROTTLE_GAIN; R_0805_2012Metric
R47: 22k_1pct_L_THROTTLE_GAIN; R_0805_2012Metric
R48: 330R_R_THROTTLE_OUTPUT; R_0805_2012Metric
R49: 6.04k_1pct_R_THROTTLE_GAIN; R_0805_2012Metric
R50: 22k_1pct_R_THROTTLE_GAIN; R_0805_2012Metric
R51: 10k_L_THROTTLE_OUTPUT_FAILSAFE; R_0805_2012Metric
R52: 10k_R_THROTTLE_OUTPUT_FAILSAFE; R_0805_2012Metric
R53: 100k_SERVO_SIGNAL_FAILSAFE; R_0805_2012Metric
U4: LTC4367IMS8#PBF; LTC4367_MSOP8
U6, U7, U8, U9: AQY212SX_60V_0.5A_PHOTOMOS; Panasonic_AQY212S_SOP4
U10: TLV9002IDR_DUAL_THROTTLE_RRIO; SOIC-8_3.9x4.9mm_P1.27mm_TLV9002
U_RGB: 74AHCT1G125; SOT-23-5
U_TRIG_F: 74AHCT1G125_TRIGGER_3V3_TO_5V; SOT-23-5
U_TRIG_L: 74AHCT1G125_TRIGGER_3V3_TO_5V; SOT-23-5
U_TRIG_R: 74AHCT1G125_TRIGGER_3V3_TO_5V; SOT-23-5

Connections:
+3V3: J3V3.1, J3V3_1.1, J3V3_2.1, J3V3_3.1, J3V3_4.1, J_ESP_R.1
+5V: C3.1, C16.1, C18.1, C21.1, C22.1, C23.1, C24.1, C27.1, F2.1, JP1V.1, JP2V.1, JP3V.1, JP4V.1, JP5V.1, JP6V.1, JP_ESP_PWR.2, J_RGB_5V.1, U10.8, U_RGB.5, U_TRIG_F.5, U_TRIG_L.5, U_TRIG_R.5
+5V_PI_FUSED: F2.2, J_PI_PWR.1, J_PI_PWR.2
+24V: C25.1, F3.1
+24V_SERVO: C19.1, D2.1, FB2.2, J_24V_AUX.1, J_SERVO.2
+24V_SERVO_FUSED: F3.2, FB2.1
AUX_GPIO2: J_ESP_R.4, U_RGB.2
BATTERY_ADC_GPIO34: C20.1, J_ESP_L.4, R41.2, R42.1
BATTERY_DIVIDER_MID: R40.2, R41.1
BAT_FUSED: D1.1, F1.2, Q5.2, R38.2, R39.1, U4.1
BAT_RAW: F1.1, J_BAT.1
ESP32_VIN_USB_ISOLATED: JP_ESP_PWR.1, J_ESP_L.15
FET_COMMON: Q5.3, Q6.3
FRONT_ECHO_GPIO: J_ESP_L.7, R5.2, R6.1
FRONT_ECHO_RAW: J_FECHO.1, R5.1
FRONT_TRIG: J_ESP_R.8, U_TRIG_F.2
FRONT_TRIG_5V: J_FTRIG.1, U_TRIG_F.4
GND: C1.2, C2.2, C3.2, C4.2, C5.1, C6.1, C7.1, C8.1, C9.1, C10.2, C11.2, C16.2, C18.2, C19.2, C20.2, C21.2, C22.2, C23.2, C24.2, C25.2, C26.2, C27.2, D1.2, D2.2, JGND3.1, JGND3_1.1, JGND3_2.1, JGND3_3.1, JGND3_4.1, JP1G.1, JP2G.1, JP3G.1, JP4G.1, JP5G.1, JP6G.1, J_24V_AUX.2, J_BAT.2, J_ESP_L.14, J_ESP_R.2, J_LCTRL_GND.1, J_PI_PWR.3, J_PI_PWR.4, J_RCTRL_GND.1, J_RGB_GND.1, J_SERVO.3, R2.2, R4.2, R6.2, R8.2, R9.2, R11.2, R15.2, R17.2, R20.1, R22.1, R24.1, R26.1, R28.1, R29.2, R30.1, R35.1, R42.2, R47.1, R50.1, R51.2, R52.1, R53.2, U4.4, U6.2, U7.2, U8.2, U9.2, U10.4, U_RGB.1, U_RGB.3, U_TRIG_F.1, U_TRIG_F.3, U_TRIG_L.1, U_TRIG_L.3, U_TRIG_R.1, U_TRIG_R.3
LEFT_ECHO_GPIO: J_ESP_L.5, R7.2, R8.1
LEFT_ECHO_RAW: J_LECHO.1, R7.1
LEFT_TRIG: J_ESP_R.3, U_TRIG_L.2
LEFT_TRIG_5V: J_LTRIG.1, U_TRIG_L.4
L_BRAKE_CONTACT_A: JP_LBRK.1, J_LBRK.1
L_BRAKE_CONTACT_A_SW: JP_LBRK.2, U7.3
L_BRAKE_CONTACT_B: J_LBRK.2, U7.4
L_BRAKE_GATE: R11.1, R12.1, U7.1
L_BRAKE_GPIO: J_ESP_L.12, R12.2
L_HALL_A_GPIO: C5.2, J_ESP_R.6, R19.1, R20.2
L_HALL_A_RAW: J_LHALLA.1, R19.2
L_HALL_B_GPIO: C6.2, J_ESP_R.7, R21.1, R22.2
L_HALL_B_RAW: J_LHALLB.1, R21.2
L_HALL_C_GPIO: C4.1, J_ESP_L.2, R1.2, R2.1
L_HALL_C_RAW: J_LHALLC.1, R1.1
L_REVERSE_CONTACT_A: JP_LREV.1, J_LREV.1
L_REVERSE_CONTACT_A_SW: JP_LREV.2, U8.3
L_REVERSE_CONTACT_B: J_LREV.2, U8.4
L_REVERSE_GATE: R15.1, R16.1, U8.1
L_REVERSE_GPIO: J_ESP_L.10, R16.2
L_THROTTLE_AMP: R45.2, U10.1
L_THROTTLE_FEEDBACK: R46.2, R47.2, U10.2
L_THROTTLE_FILTERED: C1.1, R13.1, R29.1, U10.3
L_THROTTLE_GPIO: J_ESP_L.8, R13.2
L_THROTTLE_OUT: J_LTHR.1, R45.1, R46.1, R51.1
MPU_SCL: J_ESP_R.15, J_SCL.1
MPU_SDA: J_ESP_R.5, J_SDA.1
OV_SENSE: R35.2, R36.1, U4.3
PROTECT_GATE: Q5.1, Q6.1, U4.8
PROTECT_SHDN: R39.2, U4.5
RGB_DATA_5V: R43.1, U_RGB.4
RGB_DATA_OUT: J_RGB_DATA.1, R43.2
RIGHT_ECHO_GPIO: J_ESP_L.3, R3.2, R4.1
RIGHT_ECHO_RAW: J_RECHO.1, R3.1
RIGHT_TRIG: J_ESP_R.9, U_TRIG_R.2
RIGHT_TRIG_5V: J_RTRIG.1, U_TRIG_R.4
R_BRAKE_CONTACT_A: JP_RBRK.1, J_RBRK.1
R_BRAKE_CONTACT_A_SW: JP_RBRK.2, U6.3
R_BRAKE_CONTACT_B: J_RBRK.2, U6.4
R_BRAKE_GATE: R9.1, R10.1, U6.1
R_BRAKE_GPIO: J_ESP_L.6, R10.2
R_HALL_A_GPIO: C7.2, J_ESP_R.10, R23.1, R24.2
R_HALL_A_RAW: J_RHALLA.1, R23.2
R_HALL_B_GPIO: C8.2, J_ESP_R.11, R25.1, R26.2
R_HALL_B_RAW: J_RHALLB.1, R25.2
R_HALL_C_GPIO: C9.2, J_ESP_R.14, R27.1, R28.2
R_HALL_C_RAW: J_RHALLC.1, R27.2
R_REVERSE_CONTACT_A: JP_RREV.1, J_RREV.1
R_REVERSE_CONTACT_A_SW: JP_RREV.2, U9.3
R_REVERSE_CONTACT_B: J_RREV.2, U9.4
R_REVERSE_GATE: R17.1, R18.1, U9.1
R_REVERSE_GPIO: J_ESP_L.11, R18.2
R_THROTTLE_AMP: R48.1, U10.7
R_THROTTLE_FEEDBACK: R49.1, R50.2, U10.6
R_THROTTLE_FILTERED: C2.1, R14.1, R30.2, U10.5
R_THROTTLE_GPIO: J_ESP_L.9, R14.2
R_THROTTLE_OUT: J_RTHR.1, R48.2, R49.2, R52.2
SERVO_SIG: J_ESP_L.13, J_SERVO.1, R53.1
UART_RX0_GPIO3: J_ESP_R.12, J_RX0.1
UART_TX0_GPIO1: J_ESP_R.13, J_TX0.1
UV_LOW_MID: R37.2, R38.1
UV_SENSE: R36.2, R37.1, U4.2
VIN_PROTECTED: C10.1, C11.1, C26.1, Q6.2, R40.1, U4.7

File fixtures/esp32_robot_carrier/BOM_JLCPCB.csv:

Comment,Designator,Footprint,LCSC Part #,Manufacturer,Manufacturer Part Number,Assembly Notes
"1uF 25V X7R","C1,C2",0805,,Murata,GRM21BR71E105KA99L,SMT
"1uF 50V X7R","C18,C25",1210,,KEMET,C1210C105K5RACTU,SMT; local module output bypass capacitors
"100nF 25V X7R","C3,C20,C21,C22,C23,C27",0805,,Murata,GRM21BR71E104KA01L,SMT
"10nF_HALL_RC 25V C0G","C4,C5,C6,C7,C8,C9",0805,,KEMET,C0805C103J3GACTU,SMT
"22uF 100V low-ESR","C10,C26",CP_Radial_D8_P3.5,,Panasonic,EEUFC2A220,Hand/THT; exact 8mm body and 3.5mm lead pitch
"4.7uF 100V X7R","C11",1210,,TDK,C3225X7S2A475K250AB,SMT; verify DC-bias curve
"470uF 10V low-ESR","C16",CP_Radial_D8_P3.5,,Panasonic,EEUFR1A471,Hand/THT; exact 8mm body and 3.5mm lead pitch
"470uF 50V low-ESR","C19",CP_Radial_D12.5_P5,,Panasonic,EEUFR1H471,Hand/THT; 24V servo rail; exact 12.5mm body and 5mm lead pitch
"1000uF 10V low-ESR RGB bulk","C24",CP_Radial_D10_P5,,Panasonic,EEU-FS1A102,Hand/THT; polarized; positive pad marked +
"SMCJ48A TVS","D1",SMC,,Littelfuse,SMCJ48A,SMT; unidirectional
"SMBJ26A 26V TVS","D2",SMB,,Littelfuse,SMBJ26A,SMT; unidirectional; cathode pad 1 to fused 24V servo rail
"5x20 fuse holder","F1,F2,F3",0PTF0015P,,Littelfuse,0PTF0015P,Hand/THT; fuse links ordered separately
"5A time-delay ceramic fuse 400VDC","F1_LINK,F2_LINK",5x20_cartridge,,Eaton Bussmann,S505H-5-R,Hand install; F1 is shared converter input and F2 is Pi branch; 1500A interrupt rating at 400VDC
"3.15A time-delay ceramic fuse 400VDC","F3_LINK",5x20_cartridge,,Eaton Bussmann,S505H-3.15-R,Hand install in F3 holder; dedicated 24V servo branch
"120R@100MHz 6A ferrite","FB2",1206,,Murata,BLM31KN121SN1L,SMT; 6A at 85C, 4A at 125C, 9mOhm max DCR
"36-42V battery terminal","J_BAT",PTH_2x1_5.00mm,,Phoenix Contact,1935161,Hand/THT; exact 5.00mm pitch; 17.5A nominal terminal rating
"ESP32 socket 1x15","J_ESP_L,J_ESP_R",PinSocket_1x15_P2.54mm,,Samtec,SSW-115-01-G-S,Hand/THT; two required
"Mini-Fit Jr 2x2 vertical","J_PI_PWR",MiniFitJr_2x2,,Molex,0039281043,Hand/THT; mate/housing/contacts separate
"24V servo header 1x3","J_SERVO",PinHeader_1x03_P2.54mm,,Samtec,TSW-103-07-G-S,Hand/THT; signal / fused 24V / GND; 2.5A converter limit shared with J_24V_AUX
"3.50mm terminal 1x2","J_24V_AUX,J_LBRK,J_LREV,J_RBRK,J_RREV",TerminalBlock_1x02_P3.50mm,,Phoenix Contact,1984617,Hand/THT; J_24V_AUX shares the fused 2.5A servo budget; controller contacts are floating
"Enable header 1x2","JP_LBRK,JP_LREV,JP_RBRK,JP_RREV",PinHeader_1x02_P2.54mm,,Samtec,TSW-102-07-G-S,Hand/THT; add removable shunts
"100V N-MOSFET","Q5,Q6",TO-220,,STMicroelectronics,STP100N10F7,Hand/THT; inspect orientation and insulate as required
"330R_PHOTOMOS_LED 1pct","R10,R12,R16,R18",0805,,Yageo,RC0805FR-07330RL,SMT
"330R output/data 1pct","R43,R45,R48",0805,,Yageo,RC0805FR-07330RL,SMT; RGB damping and throttle output fault limiting
"1k 1pct","R13,R14",0805,,Yageo,RC0805FR-071KL,SMT
"10k 1pct","R1,R3,R5,R7,R19,R21,R23,R25,R27,R51,R52",0805,,Yageo,RC0805FR-0710KL,SMT
"12k_1pct_HALL","R2,R20,R22,R24,R26,R28",0805,,Yageo,RC0805FR-0712KL,SMT
"15k_1pct_ULTRASONIC","R4,R6,R8",0805,,Yageo,RC0805FR-0715KL,SMT
"20k 1pct BAT ADC","R42",0805,,Yageo,RC0805FR-0720KL,SMT
"22k 1pct throttle gain","R47,R50",0805,,Yageo,RC0805FR-0722KL,SMT
"6.04k 1pct throttle gain","R46,R49",0805,,Yageo,RC0805FR-076K04L,SMT
"37.4k 1pct","R36",0805,,Yageo,RC0805FR-0737K4L,SMT
"49.9k 1pct","R35",0805,,Yageo,RC0805FR-0749K9L,SMT
"100k 1pct","R9,R11,R15,R17,R29,R30,R53",0805,,Yageo,RC0805FR-07100KL,SMT; R53 holds the 24V servo signal inactive during ESP32 reset
"240k 1pct","R40,R41",0805,,Yageo,RC0805FR-07240KL,SMT; >=50V working voltage
"470k 1pct","R39",0805,,Yageo,RC0805FR-07470KL,SMT
"2.45M 1pct","R37,R38",0805,,Yageo,RC0805FR-072M45L,SMT; series pair shares surge voltage
"74AHCT1G125 5V buffer","U_RGB,U_TRIG_L,U_TRIG_F,U_TRIG_R",SOT-23-5,C842287,Texas Instruments,SN74AHCT1G125DBVR,SMT; DBV pinout required
"Dual rail-to-rail throttle op amp","U10",SOIC-8,,Texas Instruments,TLV9002IDR,SMT; standard D-package pinout; 5V supply; both channels gain 1.2745
"60V 0.5A PhotoMOS floating contact","U6,U7,U8,U9",SOP-4,,Panasonic Industry,AQY212SX,SMT; 5mA LED drive; 1.5kVrms I/O isolation
"LTC4367 overvoltage controller","U4",MSOP-8,,Analog Devices,LTC4367IMS8#PBF,SMT
"4-position 5.08mm external buck terminal","J_BUCK_5V,J_BUCK_24V",TerminalBlock_1x04_P5.08,,Generic,KF301-5.08-4P-compatible,"Hand/THT; 4-position 5.08mm; use >=60VDC and >=10A-rated connector; pin order VIN+, VIN-, OUT-, OUT+"
"External 42V to 5V buck module","MOD_5V",Off-board,,Generic,60V+-input buck module,"Off-board; non-isolated is acceptable; input absolute max >=60V, 75V+ preferred; set output to 5.0-5.1V before connecting; >=6A verified continuous output; connect to J_BUCK_5V"
"External 42V to 24V buck module","MOD_24V",Off-board,,Generic,60V+-input buck module,"Off-board; non-isolated is acceptable; input absolute max >=60V, 75V+ preferred; set output to 24V before connecting; >=3A verified continuous output, 5A+ advertised preferred; connect to J_BUCK_24V"

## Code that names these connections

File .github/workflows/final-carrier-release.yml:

name: Final ESP32 carrier release

on:
  pull_request:
    paths:
      - 'fixtures/esp32_robot_carrier/**'
      - '.github/workflows/final-carrier-release.yml'
  workflow_dispatch:

jobs:
  release:
    runs-on: ubuntu-24.04
    steps:
      - uses: actions/checkout@v4

      - name: Reconstruct exact source board
        run: |
          set -euo pipefail
          base64 -d fixtures/esp32_robot_carrier/esp32_robot_carrier_v2.kicad_pcb.gz.b64 | gunzip > /tmp/source.kicad_pcb
          echo 'd76be0c4625d4a34c3e5a09d863da20c15aa4491002270aa1ff017080ce78dda  /tmp/source.kicad_pcb' | sha256sum -c -

      - name: Generate deterministic final board
        run: |
          set -euo pipefail
          python3 fixtures/esp32_robot_carrier/finalize_carrier.py /tmp/source.kicad_pcb /tmp/final.kicad_pcb
          echo '115f2eef607307a9be8ac29ba2bc9eb4d7db52efe347948da75c225dc191dcd3  /tmp/final.kicad_pcb' | sha256sum -c -

      - name: Validate carrier contract
        run: |
          set -euo pipefail
          python3 - <<'PY'
          from pathlib import Path
          import re
          s=Path('/tmp/final.kicad_pcb').read_text()
          required=[
            'ESP32 ROBOT CARRIER v2','5V INPUT ONLY','5V ONLY - NO 36/42V BATTERY',
            'LEFT HALL A / GPIO16','LEFT HALL B / GPIO17','LEFT HALL C / GPIO36',
            'RIGHT HALL A / GPIO19','RIGHT HALL B / GPIO21','RIGHT HALL C / GPIO22',
            'LEFT ULTRA TRIG / GPIO15','RIGHT ULTRA TRIG / GPIO18','FRONT ULTRA TRIG / GPIO5',
            'LEFT ULTRA ECHO / GPIO35','RIGHT ULTRA ECHO / GPIO39','FRONT ULTRA ECHO / GPIO34',
            'LEFT THROTTLE / GPIO25','RIGHT THROTTLE / GPIO26','LEFT BRAKE / GPIO33','RIGHT BRAKE / GPIO32',
            'LEFT REVERSE / GPIO27','RIGHT REVERSE / GPIO14','SERVO / GPIO13','ARM AUX / GPIO12','ARM AUX / GPIO2',
            'MPU6050 SDA / GPIO4','MPU6050 SCL / GPIO23','RGB LIGHTS','RGB DATA = GPIO2 -> 5V AHCT BUFFER',
            '3V3 RAIL 1','3V3 RAIL 2','3V3 RAIL 3','3V3 RAIL 4','74AHCT1G125','470uF 16V','20k','10k'
          ]
          missing=[x for x in required if x not in s]
          assert not missing, f'missing required PCB contract items: {missing}'
          nets=set(re.findall(r'\(net\s+"([^"]+)"\)',s))
          nets.update(re.findall(r'\(net\s+\d+\s+"([^"]+)"\)',s))
          for n in [
            '+5V','+3V3','GND',
            'L_BRAKE_GPIO','L_BRAKE_GATE','L_BRAKE_SW','L_BRAKE_CONN',
            'R_BRAKE_GPIO','R_BRAKE_GATE','R_BRAKE_SW','R_BRAKE_CONN',
            'L_REVERSE_GPIO','L_REVERSE_GATE','L_REVERSE_SW','L_REVERSE_CONN',
            'R_REVERSE_GPIO','R_REVERSE_GATE','R_REVERSE_SW','R_REVERSE_CONN'
          ]:
              assert n in nets, f'missing independent channel net {n}'
          qrefs=re.findall(r'\(property "Reference" "(Q\d+)"',s)
          assert len(set(qrefs)) == 4, f'expected 4 unique MOSFETs, found {sorted(set(qrefs))}'
          assert s.count('2N7002') >= 4, 'expected four 2N7002 MOSFET footprints'
          for gpio in ['GPIO33','GPIO32','GPIO27','GPIO14']:
              assert gpio in s, f'missing independent control {gpio}'
          assert '74AHCT1G125' in s, 'missing RGB 5V level shifter'
          assert '(property "Reference" "C4"' in s and '470uF 16V' in s, 'missing RGB bulk capacitor'
          print('carrier contract OK, nets',len(nets),'MOSFETs',sorted(set(qrefs)),'RGB bulk C4 OK')
          PY

      - name: Install KiCad 10
        run: |
          set -euo pipefail
          sudo add-apt-repository --yes ppa:kicad/kicad-10.0-releases
          sudo apt-get update
          sudo apt-get install --no-install-recommends -y kicad
          kicad-cli --version

      - name: Native KiCad DRC with zone refill
        run: |
          set -euo pipefail
          mkdir -p artifacts
          set +e
          kicad-cli pcb drc --severity-all --all-track-errors --refill-zones --format json --output artifacts/drc.json /tmp/final.kicad_pcb
          rc=$?
          set -e
          python3 - <<'PY'
          import json
          from collections import Counter
          d=json.load(open('artifacts/drc.json'))
          print('violations',len(d['violations']),'unconnected',len(d['unconnected_items']))
          if d['violations']:
              print(Counter(x['type'] for x in d['violations']))
          if d['violations'] or d['unconnected_items']:
              raise SystemExit(1)
          PY
          test "$rc" -eq 0

      - name: Generate fabrication files
        run: |
          set -euo pipefail
          mkdir -p artifacts/gerbers
          cp /tmp/final.kicad_pcb artifacts/esp32_robot_carrier_v2_FINAL.kicad_pcb
          kicad-cli pcb export gerbers --output artifacts/gerbers/ /tmp/final.kicad_pcb
          kicad-cli pcb export drill --output artifacts/gerbers/ /tmp/final.kicad_pcb
          test -n "$(find artifacts/gerbers -type f -name '*.gbr' -print -quit)"
          test -n "$(find artifacts/gerbers -type f \( -name '*.drl' -o -name '*.xln' \) -print -quit)"
          (cd artifacts/gerbers && zip -q ../esp32_robot_carrier_v2_JLCPCB.zip ./*)
          unzip -l artifacts/esp32_robot_carrier_v2_JLCPCB.zip

      - name: Upload manufacturing release
        if: always()
        uses: actions/upload-artifact@v4
        with:
          name: esp32-robot-carrier-v2-JLCPCB-release
          path: artifacts
          if-no-files-found: warn
